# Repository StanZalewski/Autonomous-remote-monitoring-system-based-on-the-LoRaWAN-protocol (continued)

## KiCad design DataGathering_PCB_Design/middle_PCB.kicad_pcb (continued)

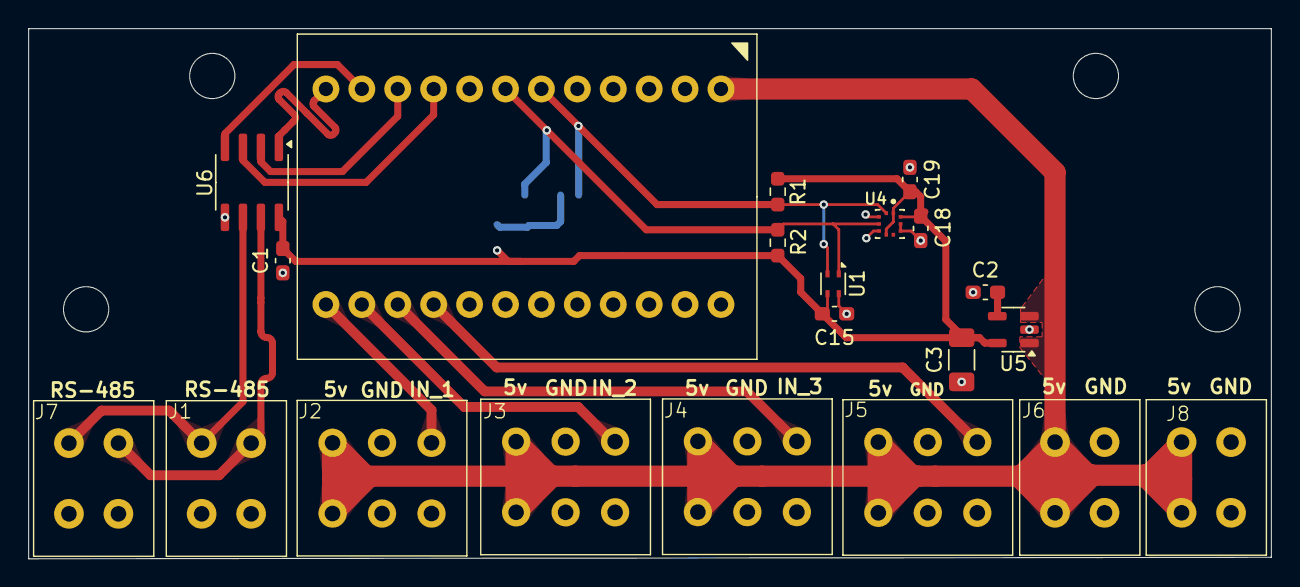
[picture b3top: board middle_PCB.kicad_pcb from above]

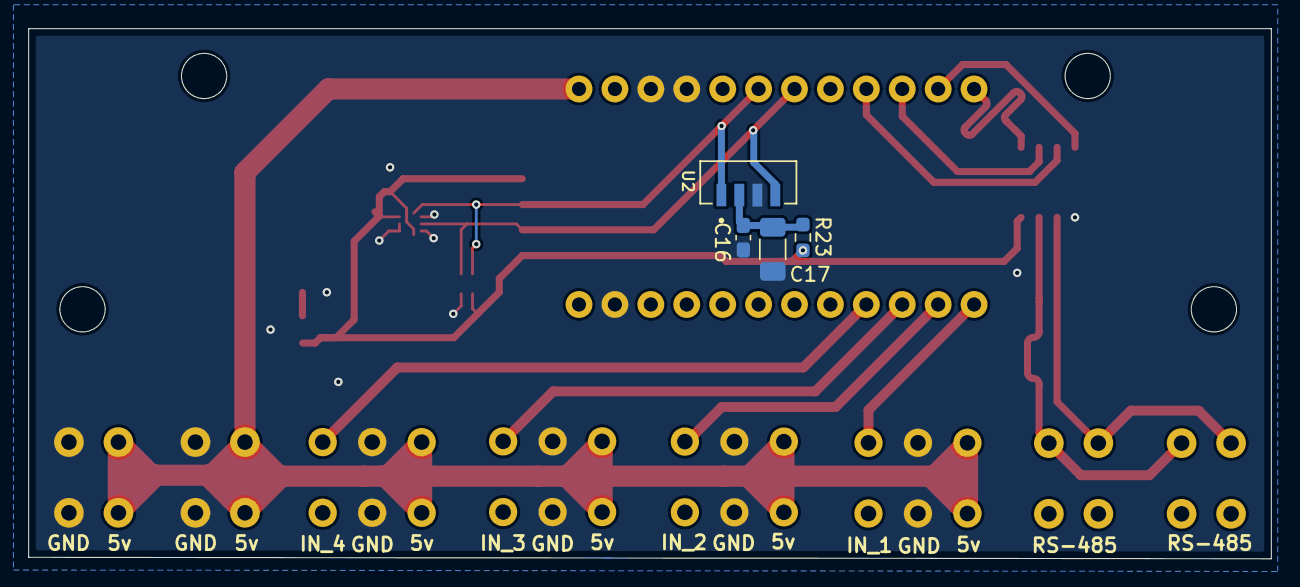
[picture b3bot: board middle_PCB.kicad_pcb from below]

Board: 2 copper layers, 87.9 x 37.5 mm, 25 parts (4 on the bottom side), 17 nets.

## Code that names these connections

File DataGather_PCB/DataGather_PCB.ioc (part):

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Mcu.Name=STM32G030F6Px
Mcu.Package=TSSOP20
Mcu.UserName=STM32G030F6Px
PA0.GPIOParameters=GPIO_Label
PA0.GPIO_Label=DE_RS485
PA0.Signal=GPIO_Output
PA1.GPIOParameters=GPIO_Label
PA1.GPIO_Label=RE_RS485
PA1.Signal=GPIO_Output
PA14-BOOT0__PA15.StandardMode=true
PA2.Mode=Asynchronous
PA2.Signal=USART2_TX
PA3.Mode=Asynchronous
PA3.Signal=USART2_RX
PA4.GPIOParameters=GPIO_Label
PA4.GPIO_Label=BIN_1
PA4.Signal=GPIO_Input
PA5.GPIOParameters=GPIO_Label
PA5.GPIO_Label=BIN_2
PA5.Signal=GPIO_Input
PA6.GPIOParameters=GPIO_Label
PA6.GPIO_Label=BIN_3
PA6.Signal=GPIO_Input
PA7.GPIOParameters=GPIO_Label
PA7.GPIO_Label=BIN_4
PA7.Signal=GPIO_Input
PB0__PB1__PB2__PA8.StandardMode=true
PB3.GPIOParameters=GPIO_Label
PB3.GPIO_Label=LED_STATE
PB3.Signal=GPIO_Output
PB3__PB4__PB5__PB6.StandardMode=true
PB7__PB8.StandardMode=true
PB8.Mode=I2C
PB8.Signal=I2C1_SCL
PB9.Mode=I2C
PB9.Signal=I2C1_SDA
PC14-OSC32_IN\ (PC14)__PB9.StandardMode=true
RCC.HSE_VALUE=8000000
RCC.SYSCLKFreq_VALUE=16000000
board=custom

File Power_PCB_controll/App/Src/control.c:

#include "control.h"
#include "main.h" 
#include "bq25798Charger.h"
#include "bq76952BMS.h"
#include "init.h" 
#include "stm32g0xx_hal_def.h"


SystemData g_system_data = {0};


HAL_StatusTypeDef GenSysInfo(void)
{
    HAL_StatusTypeDef status;
    uint8_t data[2];
    int16_t temp_kelvin;
    uint8_t temp_reg;
    
    // ========== 1. Read Cell Voltages ==========
    
    // Cell 1 Voltage (0x14)
    status = BQ76952_ReadRegister(&hi2c1, 0x14, data, 2);
    if (status != HAL_OK) return status;
    g_system_data.cell1_voltage = (int16_t)(data[0] | (data[1] << 8));
    
    // Cell 2 Voltage (0x16)
    status = BQ76952_ReadRegister(&hi2c1, 0x16, data, 2);
    if (status != HAL_OK) return status;
    g_system_data.cell2_voltage = (int16_t)(data[0] | (data[1] << 8));
    
    // Cell 3 Voltage (0x32 - Cell 16 register)
    status = BQ76952_ReadRegister(&hi2c1, 0x32, data, 2);
    if (status != HAL_OK) return status;
    g_system_data.cell3_voltage = (int16_t)(data[0] | (data[1] << 8));
    
    // ========== 2. Read Current ==========
    
    // Read CC2 Current (0x3A) - Signed, in mA
    status = BQ76952_ReadRegister(&hi2c1, 0x3A, data, 2);
    if (status != HAL_OK) return status;
    g_system_data.current_pack = (int16_t)(data[0] | (data[1] << 8));
    
    // ========== 3. Read Pack Temperature BMS Side ==========
    
    // Read TS1 Temperature (0x70) - Returns 0.1K
    status = BQ76952_ReadRegister(&hi2c1, 0x70, data, 2);
    if (status != HAL_OK) return status;
    temp_kelvin = (int16_t)(data[0] | (data[1] << 8));
    
    // Convert from 0.1K to 0.1°C (subtract 273.1 * 10 = 2731)
    g_system_data.pack_temperature_BMS = temp_kelvin - 2731;

    // ========== 4. Read Charger Temperature ==========
    
    // Read TS_ADC (0x3F - BQ25798) - Returns percentage (0-99.9023%)
    status = BQ25798_ReadRegister(&hi2c1, 0x3F, data, 2);
    if (status != HAL_OK) return status;
    uint16_t ts_adc_raw = (uint16_t)((data[0] << 8) | data[1]);
    
    // Convert to percentage: percentage = raw_value × 0.0976563%
    // For storage as integer (0.1% resolution): percentage_tenth = raw_value * 0.976563
    // Or just store raw value for now
    g_system_data.pack_temperature_Charger = (int16_t)ts_adc_raw;
    
    // ========== 5. Read VAC1 Voltage (BQ25798 - BIG ENDIAN!) ==========
    
    // Read VAC1_ADC (0x37 - BQ25798) - MSB FIRST!
    status = BQ25798_ReadRegister(&hi2c1, 0x37, data, 2);
    if (status != HAL_OK) return status;
    g_system_data.vac1_voltage = (uint16_t)((data[0] << 8) | data[1]);
    
    
    // ========== 6. Build gen_sys_status Byte ==========
    
    g_system_data.gen_sys_status = 0;
    
    // Bit 0: CHG FET Status (DCHG pin on PA5)
    // DCHG is an active-low "disable charge" output, so pin HIGH = CHG FET ON
    if (HAL_GPIO_ReadPin(DCHG_GPIO_Port, DCHG_Pin) == GPIO_PIN_SET) {
        g_system_data.gen_sys_status |= (1 << 0);
    }
    
    // Bit 1: DSG FET Status (DDSG pin on PA4)
    // DDSG is an active-low "disable discharge" output, so pin HIGH = DSG FET ON
    if (HAL_GPIO_ReadPin(DDSG_GPIO_Port, DDSG_Pin) == GPIO_PIN_SET) {
        g_system_data.gen_sys_status |= (1 << 1);
    }
    
    // Bit 2: MPPT Status (from MPPT_Control register 0x15, bit 0 = EN_MPPT)
    status = BQ25798_ReadRegister(&hi2c1, 0x15, &temp_reg, 1);
    if (status != HAL_OK) return status;
    if (temp_reg & 0x01) {  // Bit 0 = EN_MPPT
        g_system_data.gen_sys_status |= (1 << 2);
    }
    
    // Bit 3: Battery Presence Status (from charger_status_2, bit 0)
    // Copy bit 0 from g_charger_status.charger_status_2 to bit 3
    if (g_charger_status.charger_status_2 & 0x01) {
        g_system_data.gen_sys_status |= (1 << 3);
    }
    
    // Bit 4: Watchdog Status (from charger_status_0, bit 5)
    // Bit 5 of charger_status_0 (REG0x1B) is WD_STAT
    // Copy bit 5 to bit 4 of gen_sys_status
    if (g_charger_status.charger_status_0 & (1 << 5)) {
        g_system_data.gen_sys_status |= (1 << 4);
    }
    
    // Bits 5-7: Charger Status (CHG_STAT from charger_status_1 bits 7:5)
    // Extract bits 7:5 and shift to bits 7:5 of gen_sys_status
    uint8_t chg_stat = (g_charger_status.charger_status_1 >> 5) & 0x07;  // Get bits 7:5
    g_system_data.gen_sys_status |= (chg_stat << 5);  // Place in bits 7:5
    
    return HAL_OK;
}



void WatchDogs_R (void)
{
    BQ25798_SetChargerControl_1(&hi2c1, TIMER_80s, WD_RESET, VAC_OVP_26V, VINDPM_60P);
}

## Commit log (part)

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2026-05-18 Initial commit: embedded firmware and PCB design files for all three modules
